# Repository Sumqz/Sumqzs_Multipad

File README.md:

# Sumqzs_Multipad

First up sorry for any typos or grammar mistakes. English isn't my primary language but I've tried my best.

My own custom macropad. It's simple but includes a variety of features. It's supposed to make life with a 60% keyboard better. You get the space benefit of a small keyboard but still have extra buttons and features when needed. This project was made possible by blueprint.hackclub.

I made this product following the tutorial on blueprint.hackclub and added my own ideas. I've had a lot of fun and will probably be making another project soon.

If anyone wants to build something similar feel free to ask me about the process!

---

## Bill of Materials (BOM)

Here are all of the products used (example parts):

| Part | Quantity | Description | Part Number | Link |
|------|----------|-------------|-------------|------|
| Microcontroller | 1 | Seeed Studio XIAO RP2040 | XIAO-RP2040 | https://www.amazon.com/Microcontroller-Dual-Core-MicroPython-CircuitPython-Interfaces/dp/B09NNVNW7M |
| OLED Display | 1 | 0.91" I2C OLED 128x32 (SSD1306) | SSD1306 0.91" | https://www.ziotester.it/elettronica/display/ssd1306-display-oled-0-91-pollici-128-32-pixel.html |
| Mechanical Switch | 6 | PCB mount mechanical switch | Cherry MX compatible | https://www.cherry.de/en-gb/products/switches/mx-standard |
| Rotary Encoder | 1 | ALPS EC11 with push button | EC11E15244G1 | https://tech.alpsalpine.com/e/products/detail/EC11E15244G1/ |
| RGB LED | 2 | SK6812 Mini-E RGB LED | SK6812MINI-E | https://www.adafruit.com/product/4960 |
| PCB | 1 | Custom PCB | – | https://jlcpcb.com |
| Case (3D Print) | 1 | 3D printed enclosure | – | – |

Note: The linked parts are example references. Please double-check compatibility before ordering parts for your own build.

---

## Pictures

### Assembled (Top)

### Assembled (Angled View)

### Side View

### With Lid

---

## Schematic

Changed it to a matrix to make room for all the switches!
## PCB

## Case Design / 3D Model

---

## PCB Price

---

All needed files are included in the repository. Other files are sorted in folders.

The firmware is still not finished and will be updated once the parts are assembled.

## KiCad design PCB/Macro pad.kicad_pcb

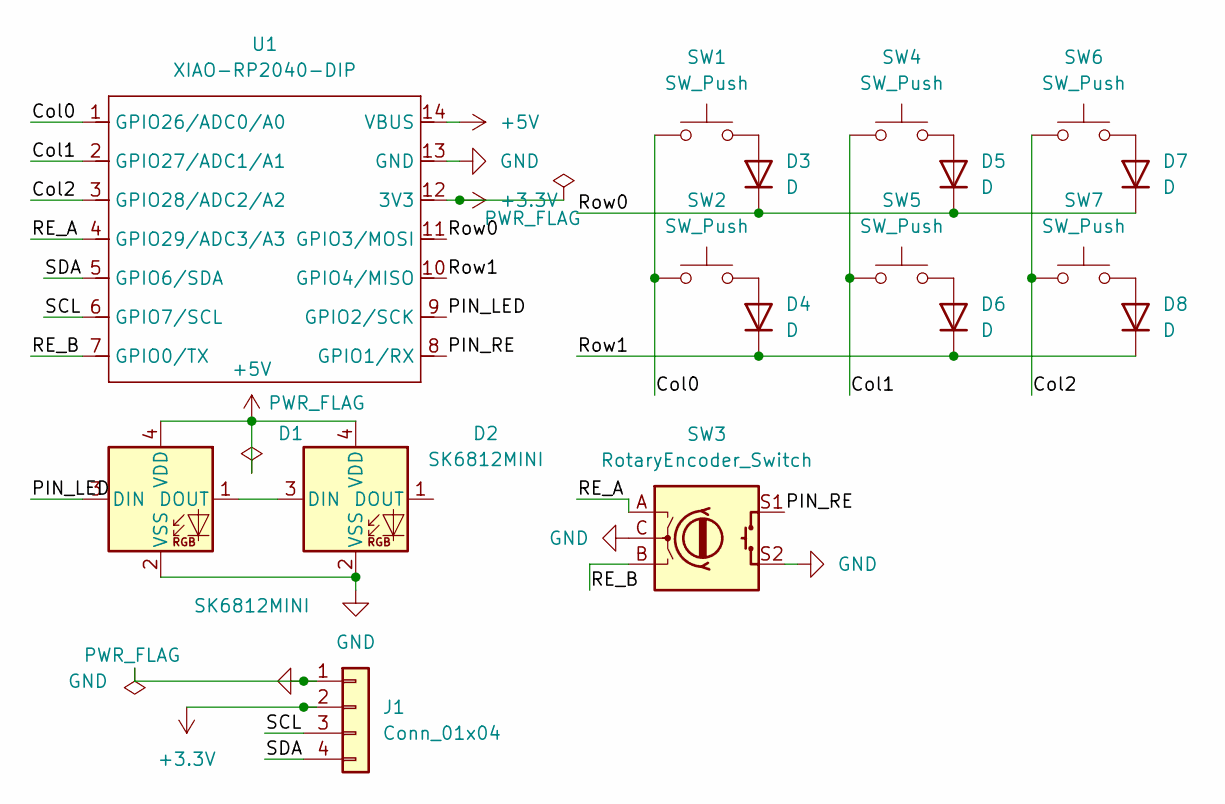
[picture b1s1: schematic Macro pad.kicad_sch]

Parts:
D1, D2: SK6812MINI; SK6812MINI-E_fixed
D3, D4, D5, D6, D7, D8: D; D_DO-35_SOD27_P7.62mm_Horizontal
J1: Conn_01x04; FanPinHeader_1x04_P2.54mm_Vertical
SW1, SW2, SW4, SW5, SW6, SW7: SW_Push; SW_Cherry_MX_1.00u_PCB
SW3: RotaryEncoder_Switch; RotaryEncoder_Alps_EC11E-Switch_Vertical_H20mm
U1: XIAO-RP2040-DIP

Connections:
+3.3V: J1.2, U1.12 (3V3)
+5V: D1.4 (VDD), D2.4 (VDD), U1.14 (VBUS)
/Col0: SW1.1, SW2.1, U1.1 (GPIO26/ADC0/A0)
/Col1: SW4.1, SW5.1, U1.2 (GPIO27/ADC1/A1)
/Col2: SW6.1, SW7.1, U1.3 (GPIO28/ADC2/A2)
/PIN_LED: D1.3 (DIN), U1.9 (GPIO2/SCK)
/PIN_RE: SW3.S1, U1.8 (GPIO1/RX)
/RE_A: SW3.A, U1.4 (GPIO29/ADC3/A3)
/RE_B: SW3.B, U1.7 (GPIO0/TX)
/Row0: D3.1 (K), D5.1 (K), D7.1 (K), U1.11 (GPIO3/MOSI)
/Row1: D4.1 (K), D6.1 (K), D8.1 (K), U1.10 (GPIO4/MISO)
/SCL: J1.3, U1.6 (GPIO7/SCL)
/SDA: J1.4, U1.5 (GPIO6/SDA)
GND: D1.2 (VSS), D2.2 (VSS), J1.1, SW3.C, SW3.S2, U1.13 (GND)
unnamed: D1.1 (DOUT), D2.3 (DIN)
unnamed: D3.2 (A), SW1.2
unnamed: D4.2 (A), SW2.2
unnamed: D5.2 (A), SW4.2
unnamed: D6.2 (A), SW5.2
unnamed: D7.2 (A), SW6.2
unnamed: D8.2 (A), SW7.2

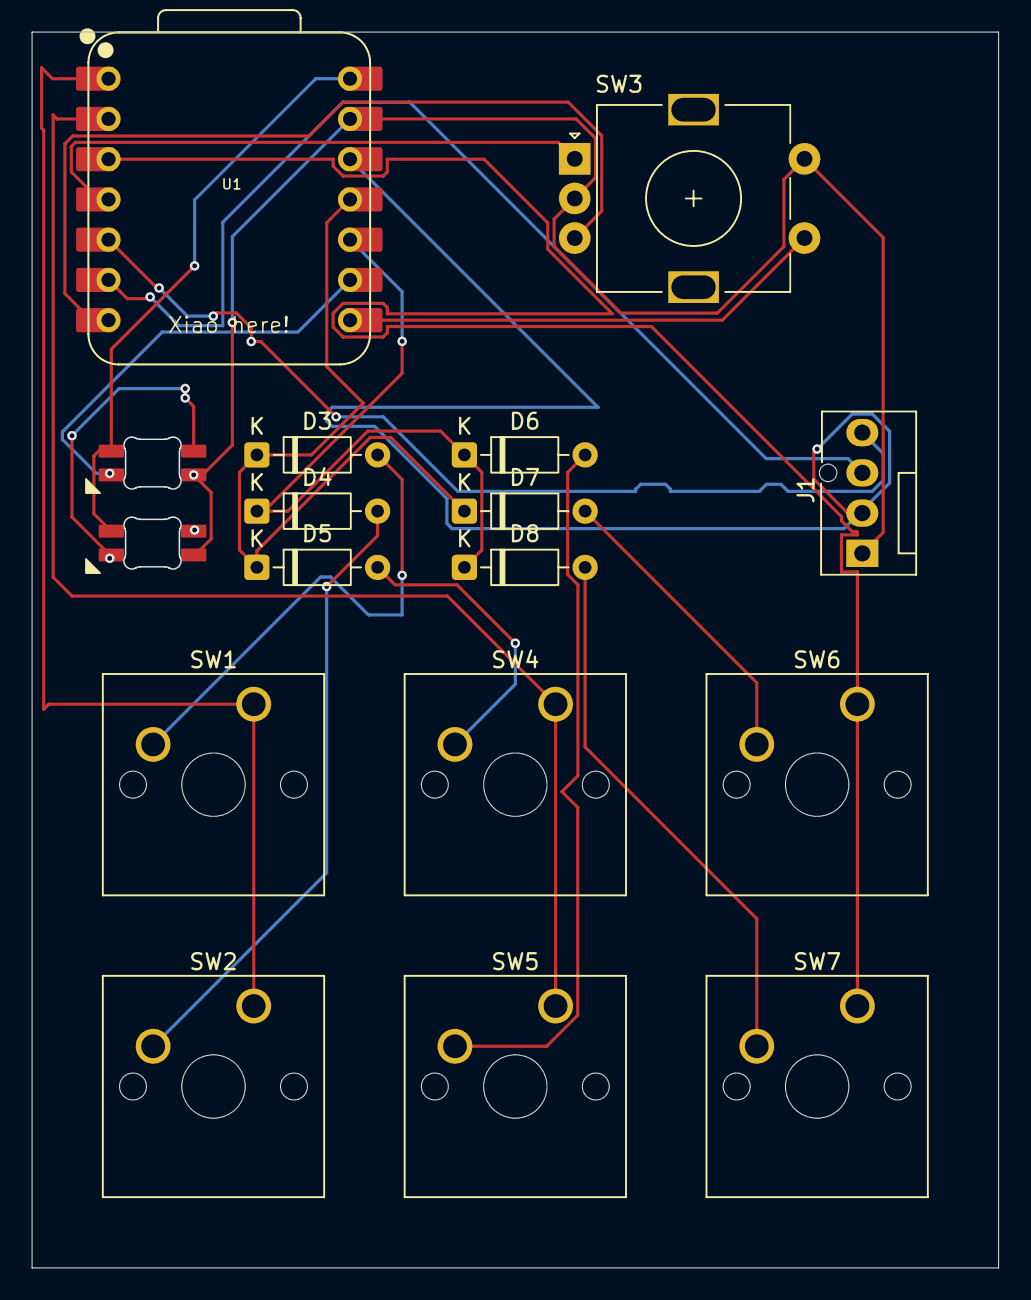
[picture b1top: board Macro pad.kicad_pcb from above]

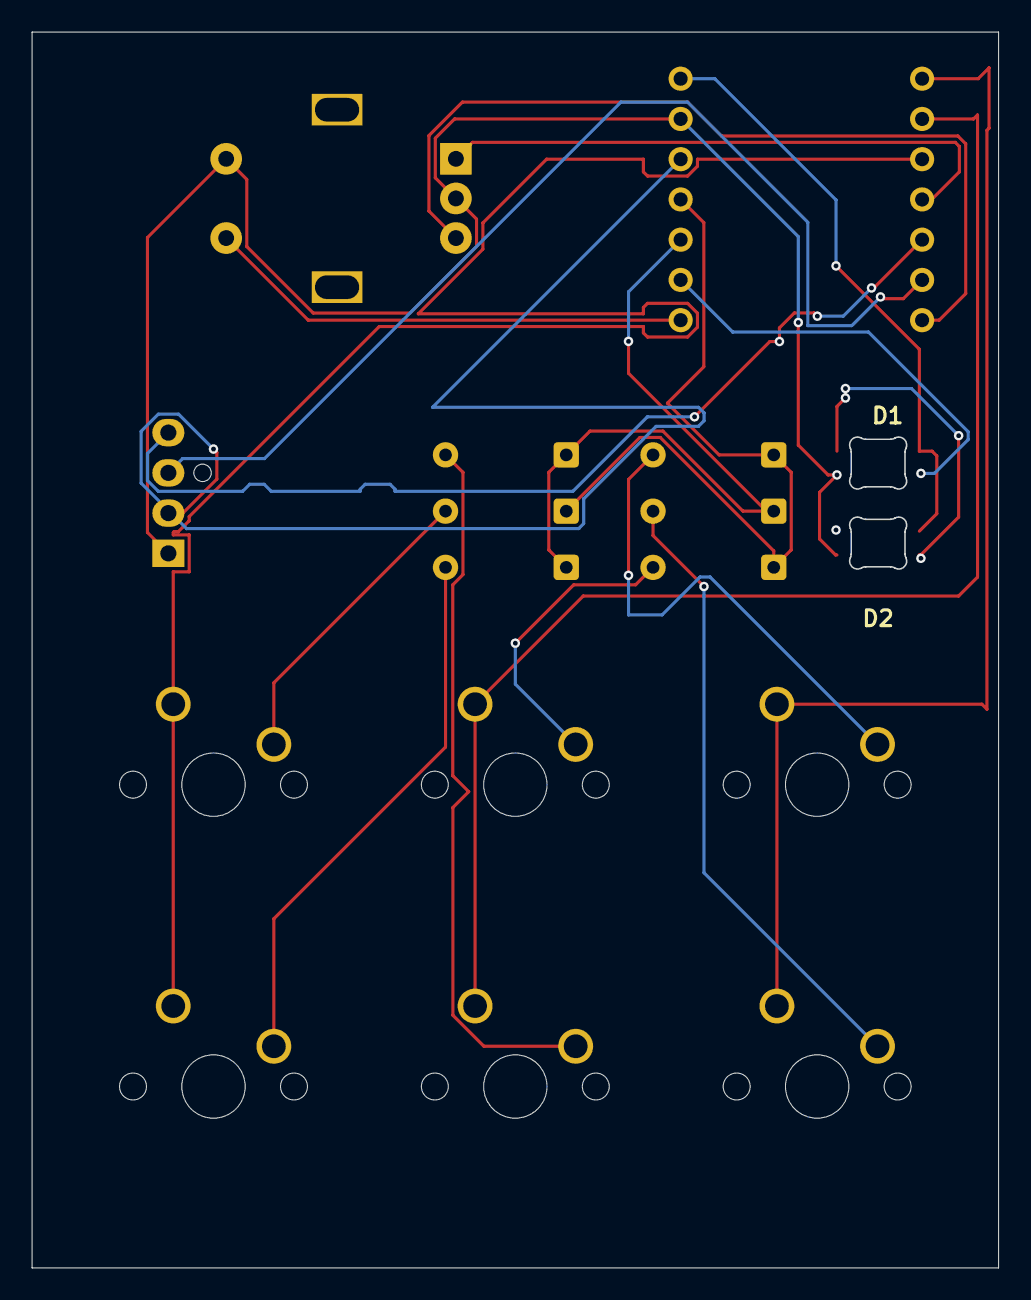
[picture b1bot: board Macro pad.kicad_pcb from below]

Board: 2 copper layers, 61.0 x 78.0 mm, 17 parts (2 on the bottom side), 21 nets.

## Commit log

2026-02-05 Initial commit: baseline firmware and production UF2
2026-02-05 added pictures
2026-02-05 Update README with project details and images
    Expanded project description, added bill of materials, images, and notes on firmware.
2026-02-05 Update README to include language proficiency note
    Added a note about potential typos and grammar mistakes due to language proficiency.
2026-02-06 Update README to clarify PCB price location
2026-02-06 Enhance README with Bill of Materials section
    Added a detailed Bill of Materials (BOM) section with product links and descriptions.
2026-02-06 Revise Bill of Materials for clarity and consistency
    Updated the Bill of Materials section to improve clarity and consistency.
2026-02-06 Revise product links and add verification disclaimer
    Updated product links in the README with new sources and added a disclaimer about product verification.
2026-02-08 Added step files to the CAD folder
2026-02-08 Clarify PCB layout image update note
    Updated the PCB layout image note for clarity.
2026-02-10 Revise README for clarity and add BOM section
    Corrected grammar and improved clarity in the README. Added a Bill of Materials (BOM) section with example parts and links. Included pictures and schematic details.
2026-02-12 Clarify rotary encoder connection in README
    Added note about rotary encoder connections in schematic section.
2026-02-14 Fix schematic image filename case in README
    Corrected the filename case for the schematic image in README.
2026-02-14 Clarify rotary encoder and PCB layout in README
    Updated the README to clarify rotary encoder connections and PCB layout changes.
2026-02-14 Fix formatting of PCB section in README
2026-02-14 Fix schematic image filename in README
    Corrected the image filename for the schematic.
2026-02-14 Fix schematic image filename in README
    Corrected the filename of the schematic image.
